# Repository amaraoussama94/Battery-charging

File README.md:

# Battery-charging
KiCad project

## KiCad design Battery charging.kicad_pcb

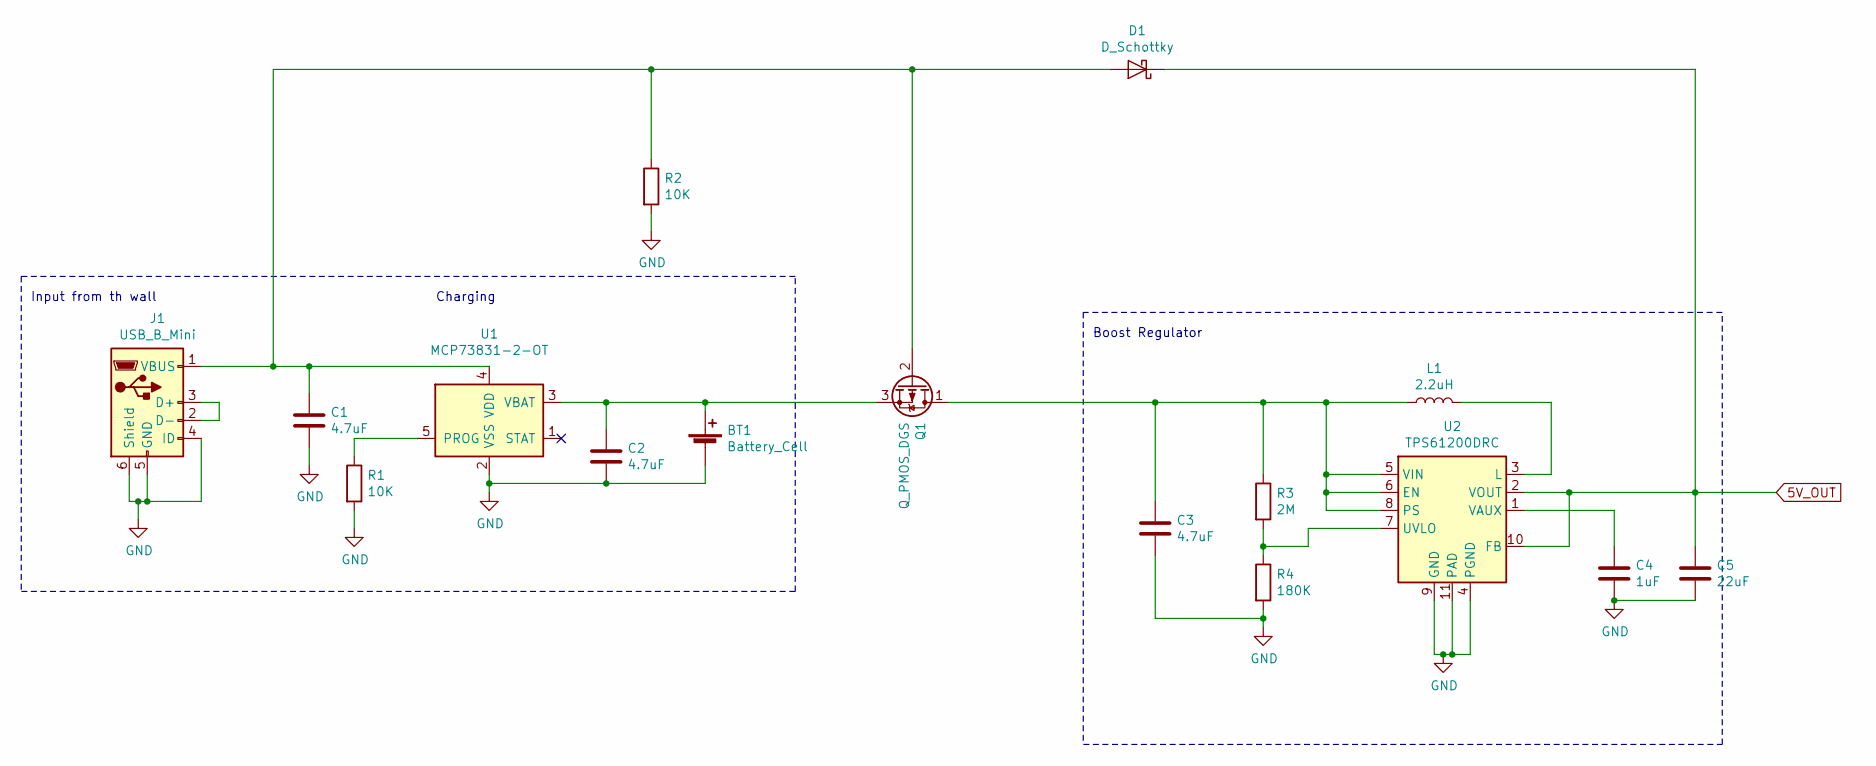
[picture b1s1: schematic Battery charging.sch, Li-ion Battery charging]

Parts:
BT1: Battery_Cell; BatteryHolder_Eagle_12BH611-GR
C1, C2, C3: 4.7uF; CP_Elec_4x4.5
C4: 1uF; CP_Elec_3x5.3
C5: 22uF; CP_Elec_6.3x5.2
D1: D_Schottky; D_5W_P12.70mm_Horizontal
J1: USB_B_Mini; USB_Mini-B_Lumberg_2486_01_Horizontal
L1: 2.2uH; L_Axial_L14.0mm_D4.5mm_P7.62mm_Vertical_Fastron_LACC
Q1: Q_PMOS_DGS; SuperSOT-3
R1, R2: 10K; R_Axial_DIN0207_L6.3mm_D2.5mm_P10.16mm_Horizontal
R3: 2M; R_Axial_DIN0207_L6.3mm_D2.5mm_P10.16mm_Horizontal
R4: 180K; R_Axial_DIN0207_L6.3mm_D2.5mm_P10.16mm_Horizontal
U1: MCP73831-2-OT; SOT-23-5
U2: TPS61200DRC; Texas_S-PVSON-N10_ThermalVias

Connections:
5V_OUT: C5.1, D1.1 (K), U2.2 (VOUT), U2.10 (FB)
GND: BT1.2 (-), C1.2, C2.2, C3.2, C4.2, C5.2, J1.4 (ID), J1.5 (GND), J1.6 (Shield), R1.2, R2.2, R4.2, U1.2 (VSS), U2.4 (PGND), U2.9 (GND), U2.11 (PAD)
unnamed: BT1.1 (+), C2.1, Q1.3 (S), U1.3 (VBAT)
unnamed: C1.1, D1.2 (A), J1.1 (VBUS), Q1.2 (G), R2.1, U1.4 (VDD)
unnamed: C3.1, L1.1, Q1.1 (D), R3.1, U2.5 (VIN), U2.6 (EN), U2.8 (PS)
unnamed: C4.1, U2.1 (VAUX)
unnamed: J1.2 (D-), J1.3 (D+)
unnamed: L1.2, U2.3 (L)
unnamed: R1.1, U1.5 (PROG)
unnamed: R3.2, R4.1, U2.7 (UVLO)

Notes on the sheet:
Boost Regulator
Input from th wall
Charging

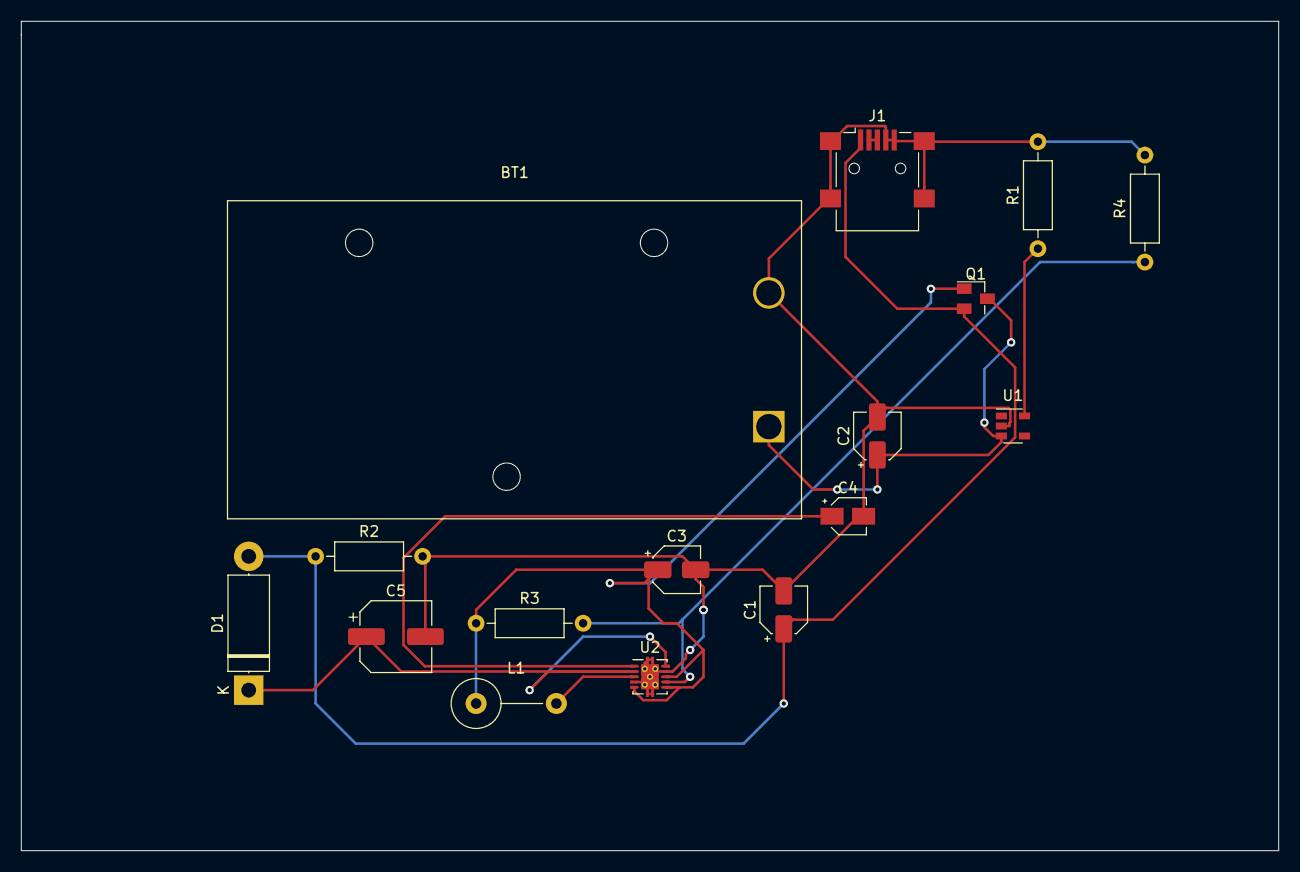
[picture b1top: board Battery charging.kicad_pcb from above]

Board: 2 copper layers, 119.4 x 78.7 mm, 16 parts (0 on the bottom side), 10 nets.
